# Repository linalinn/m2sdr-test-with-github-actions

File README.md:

# m2sdr

### top

### bottom

## spaces
### top

### bottom

### rotated markdown

### rotated html

<video src="https://linalinn.github.io/m2sdr/rotating.mp4" width="40" height="40" />

<video width="320" height="329" controls>
  <source src="https://linalinn.github.io/m2sdr-test-with-github-actions/rotating.mp4" type="video/mp4">
</video>

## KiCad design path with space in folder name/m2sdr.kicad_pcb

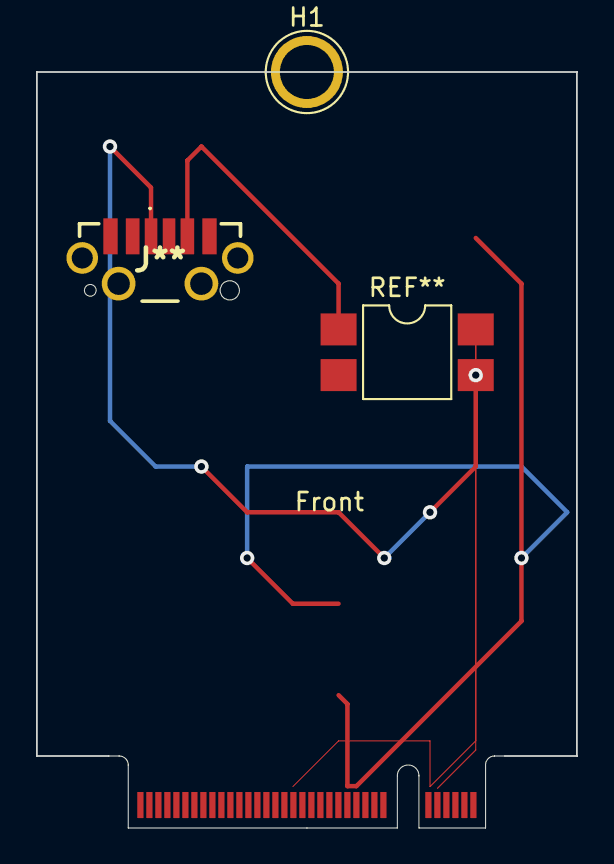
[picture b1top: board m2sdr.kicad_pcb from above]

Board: 2 copper layers, 30.0 x 42.0 mm, 3 parts (0 on the bottom side), 2 nets.

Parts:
H1: MountingHole_Pad; TestPoint_Plated_Hole_D3.0mm
J1: Bus_M.2_Socket_B; NGFF_B
J**: USB4140GF0170C

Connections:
GND: H1.1, J1.3 (GND), J1.5 (GND), J1.11 (GND), J1.27 (GND), J1.33 (GND), J1.39 (GND), J1.45 (GND), J1.51 (GND), J1.57 (GND), J1.71 (GND), J1.73 (GND)
unnamed: J1.2 (3.3V), J1.4 (3.3V), J1.70 (3.3V), J1.72 (3.3V), J1.74 (3.3V)

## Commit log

2024-02-23 Add github action to render pcb images to github pages
2024-02-23 move images.yaml into workflow dir
2024-02-23 Add checkout repo
2024-02-23 switch to image containg kicad config
2024-02-23 add continue-on-error ture
2024-02-23 add more continue-on-error: true
2024-02-23 add || exit 0 ro upload error.png
2024-02-23 switch main to master
2024-02-23 upload error.png
2024-02-23 upload all
2024-02-25 switch to image tag newclipara
2024-02-25 Add --debug-path to pcbdraw render
2024-02-25 upload images to github pages
2024-02-25 output images into images folder
2024-02-27 tripple timeout
2024-02-27 reduce timeout to x2 the defaults
2024-02-27 back to 3
2024-02-27 timeout x4
2024-02-27 Add readme
2024-02-29 add --debug-print
2024-03-01 add debug out
2024-03-01 add footprint for testing
2024-03-12 switch to github action
2024-03-12 use github.workspace
2024-03-24 render mp4 animation
2024-03-26 Add some components and copy in path with space in folder name
2024-03-26 add image render for path with sapces
2024-03-26 update links
2026-03-20 test kicad-10-upgrade branch
2026-03-20 Update configure-pages action to version 4
2026-03-20 Upgrade upload-pages-artifact action to v4
